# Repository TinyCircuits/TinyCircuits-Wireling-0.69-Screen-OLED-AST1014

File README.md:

# TinyCircuits Wireling 0.69 Screen OLED
# AST1014 Rev1

The design files are located under design_files/ for the TinyCircuits AST1014 Rev 1 PCB. This is a Wireling board which features a 96x16 pixel White Monochrome OLED display which can be controlled using the TinyCircuits TinierScreen library.

Format is in Cadsoft Eagle format - Eagle version 6.2 was used for the original design.

For more infomation on this, check out the product page at TinyCircuits.com

# License:

Design by TinyCircuits.
All design files are released under the Creative Commons Attribution Share-Alike 3.0 License, see the following link for details: http://creativecommons.org/licenses/by-sa/3.0

All text above must be included in any redistribution or derived design

This project uses designs and concepts developed as part of the Arduino project and the LilyPad project.  The TinyCircuits design files themselves (schematics, PCB and libraries) are not directly derived from these works' design files and have been created new, however the concepts and basic architecture behind the TinyDuino and TinyLily products are derived and we thank the hard work of the organizations below for their contributions to open-source hardware:
  
Original Arduino Uno Design by Team Arduino

LilyPad Arduino Design by Leah Buechley and Sparkfun Electronics

Please support the open-source hardware community

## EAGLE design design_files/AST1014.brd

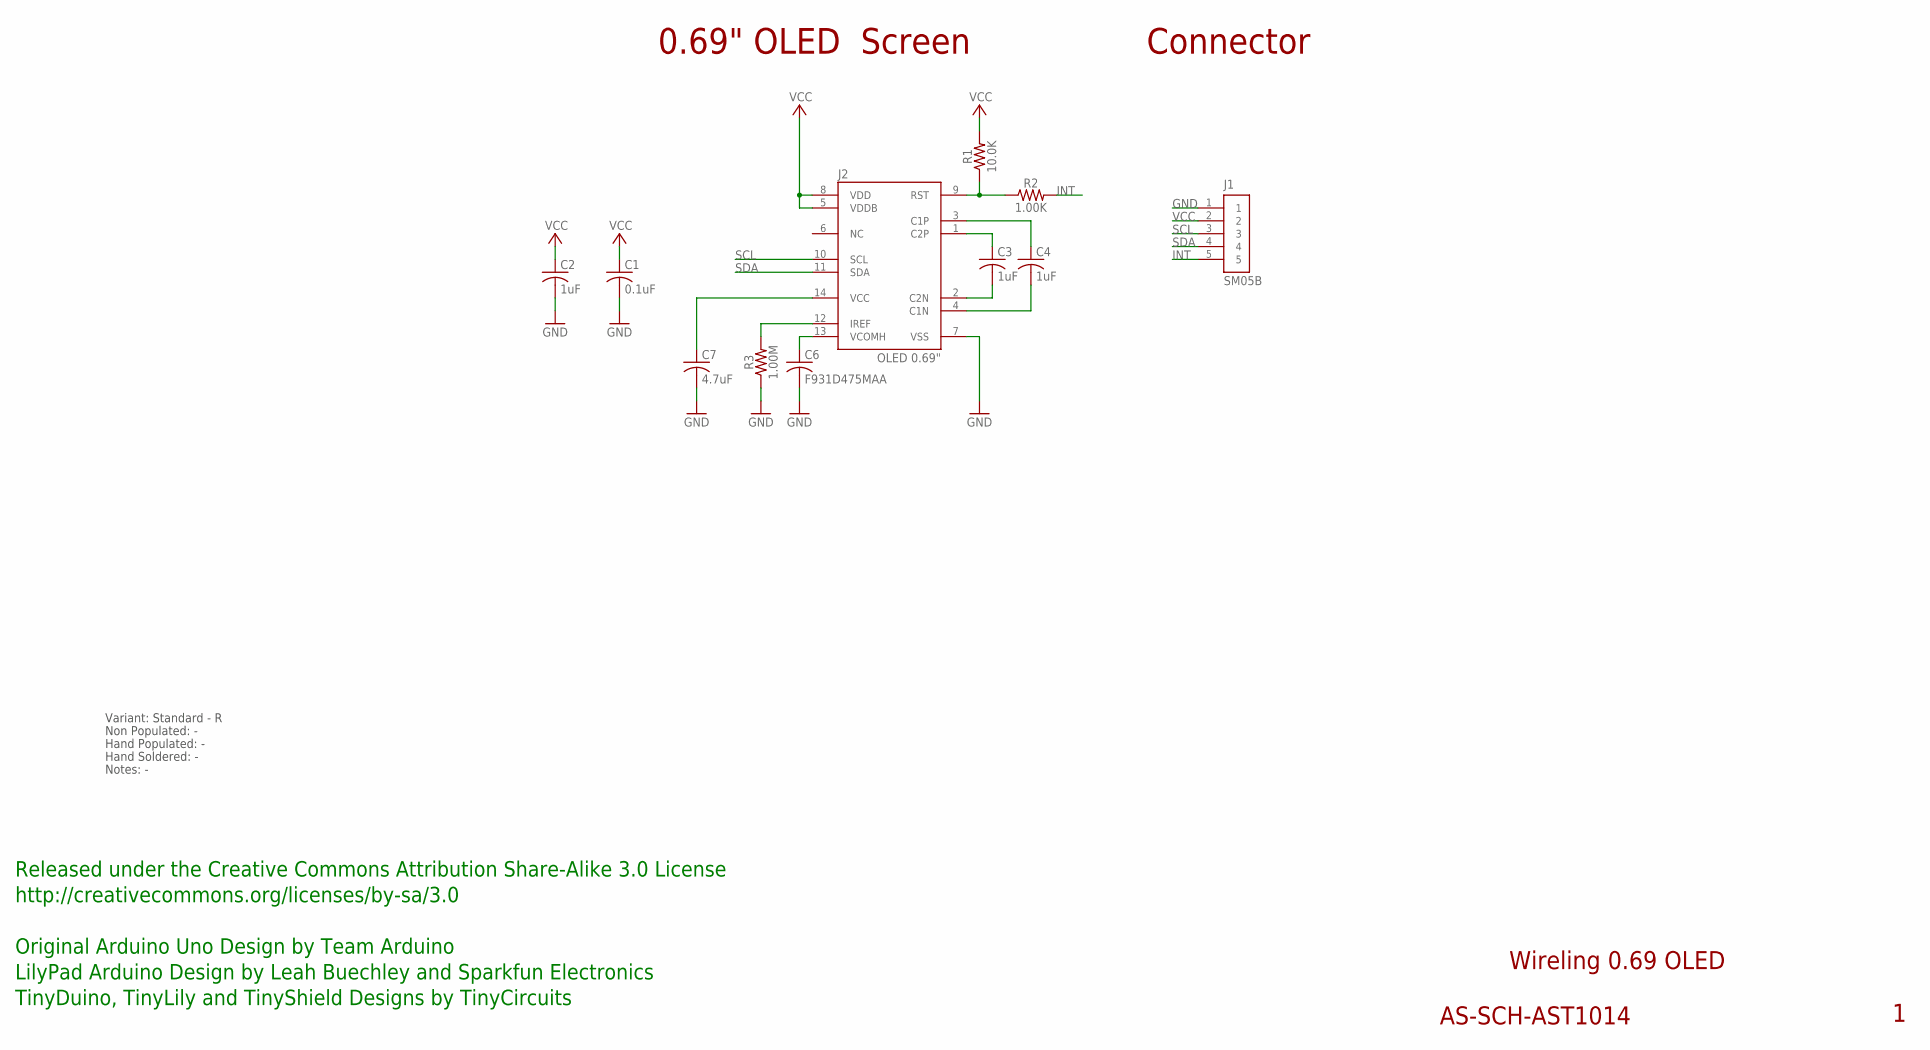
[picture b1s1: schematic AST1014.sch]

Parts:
C1: 0.1uF; C0402
C2: 1uF; C0603; PARTNO AS-ITM-00347
C3, C4: 1uF; C0603
C6: F931D475MAA; 1206_CAP_TANT
C7: 4.7uF; C0603
J1: SM05B; JST_SH_5X1
J2: OLED 0.69"; OLED_WHITE_0.69"
R1: 10.0K; 0402
R2: 1.00K; 0402; PARTNO AS-ITM-00003
R3: 1.00M; 0402

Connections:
GND: C1.2, C2.2, C6.2, C7.2, J1.1, J2.7 (VSS), R3.1
INT: J1.5, R2.2
unnamed: C3.1, J2.1 (C2P)
unnamed: C6.1, J2.13 (VCOMH)
unnamed: C3.2, J2.2 (C2N)
unnamed: C4.2, J2.4 (C1N)
unnamed: C4.1, J2.3 (C1P)
unnamed: C7.1, J2.14 (VCC)
unnamed: J2.12 (IREF), R3.2
unnamed: J2.9 (RST), R1.1, R2.1
SCL: J1.3, J2.10 (SCL)
SDA: J1.4, J2.11 (SDA)
VCC: C1.1, C2.1, J1.2, J2.5 (VDDB), J2.8 (VDD), R1.2

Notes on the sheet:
Wireling 0.69 OLED
AS-SCH-AST1014
0.69" OLED Screen
Released under the Creative Commons Attribution Share-Alike 3.0 License
http://creativecommons.org/licenses/by-sa/3.0
Original Arduino Uno Design by Team Arduino
TinyDuino, TinyLily and TinyShield Designs by TinyCircuits
LilyPad Arduino Design by Leah Buechley and Sparkfun Electronics
Connector
Non Populated: -
Hand Populated: -
Hand Soldered: -
Notes: -
Variant: Standard - R

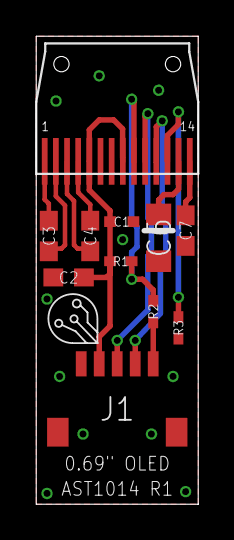
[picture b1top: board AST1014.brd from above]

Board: 2 copper layers, 9.0 x 26.0 mm, 12 parts (0 on the bottom side), 13 nets.

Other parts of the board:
U$1: DOCFIELD-TINYCIRCUITS-PCB

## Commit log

2019-08-01 bye json
2019-08-05 added datasheet
2019-09-30 fix program
2019-12-17 updated documentation
2020-02-04 mass image update
2020-02-27 lib update
2020-03-09 remove old example
2020-05-19 added correct datasheet
2020-08-14 Add CAD data
